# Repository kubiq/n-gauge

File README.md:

# N Gauge

A round AMOLED gauge that lives in the driver-side air vent of a **Hyundai
i30 N**, reading the car live over the OBD-II port: **oil temperature** - the
number the car's own dashboard hides behind a menu - plus coolant, boost, tyre
pressures, a g-meter, GPS speed and a lap timer. It logs every drive to an SD
card, uploads the logs home by itself as the car starts - over the phone's
hotspot and a WireGuard VPN - and a phone app pulls them off it and shows
each drive on a map.

Everything here was built for one car and is in daily use in it. It is a
hobby project, published in case the findings, the code or the approach help
someone with the same car or the same board.

*From the driver's seat, beside the car's own cluster; and switched off - the
3D-printed housing replaces the left air vent's surround.*

*The phone app: every drive, named after where it went and grouped by week,
with the gauge in the header - its last sync, like a watch in Garmin
Connect; a tap on it syncs, then the phone is back on the internet. A drive
on the map, coloured by speed, and its speed, boost, temperatures and
voltage over time. More in [mobile/](mobile).*

*The gauge's screens - oil and coolant, boost, the g-meter, tyres, GPS, and
the lap timer 1.8 s up on the best lap, the arc filling up to the line - then
the oil over its warning on the in-lap, a red rim over whichever screen is
up, and the N badge it wakes up with. Swiped through on the gauge; these are
from the [simulator](sim) on a made-up track session (`sim/screenshots.sh`).*

## What it does

- **Gauges:** oil and coolant (concentric arcs, with a cold-engine "not
  ready" state, and over-temperature warnings on every screen), boost, a
  g-meter, the four tyre pressures and temperatures, GPS speed and trip
  distance, a lap timer that finds the start/finish line by itself (tap START
  in the pit, then drive), with how far the line is and the live delta to the
  best lap.
- **Logging:** a CSV of every drive (2 Hz, decoded values - battery voltage,
  fuel rate, lambda, catalyst and fuel rail among them), a GPX track at
  25 Hz, a sleep log, and for each track session a Racelogic `.vbo` with
  every channel, which lap analysers open (HackTheTrack, Circuit Tools).
  Logs can be encrypted to a key only the phone holds, so a card taken out of
  the gauge gives nothing away. GPS points are kept only while the car talks
  or really moves, so a parked car's GPS drift is not a drive.
- **Upload home:** as the car starts - in the garage or setting off, where
  the GPS matters least - the gauge joins the phone's hotspot (a phone
  routine turns it on when it connects to the car's Bluetooth), opens a
  WireGuard tunnel into the home network and sends a small service on the
  home server ([server/](server)) whatever it lacks, resuming where the last
  upload stopped. The logs go as encrypted as they are on the card. Set up
  once in the app: the hotspot, the VPN (the gauge makes its own key; the app
  shows its public half for the router) and the server, with a time limit
  for how long the hotspot is the gauge's. Measured first, with a test build:
  transmitting costs ~6 dB of GNSS signal at any WiFi power, so it happens
  in the seconds an upload takes, not the whole drive. An optional status
  screen shows where it is - the hotspot, the VPN, the firmware download,
  the logs sent - and what came of the last one.
- **Waking up:** the N badge until the car answers, so the gauges never
  show a row of dashes; with a PC on USB, a status page for the desk.
- **Power:** deep sleep when the car goes quiet, ~11 mA parked (about 57
  days on the battery); wakes on CAN activity, the button, or the door
  opening (the IMU's wake-on-motion).
- **Firmware updates:** from the phone, the SD card or - by itself, after
  each upload of the logs, resuming a download that was cut off - the home
  server, signed (Ed25519) so it installs nothing else; on probation, rolled
  back if the new one fails.
- **Phone:** its own WiFi access point - with the upload set up, only once
  swiped to on the gauge, so the radio is free otherwise - with settings
  pages, OTA firmware
  updates with rollback, and an Android app ([mobile/](mobile)) that joins it
  from a QR code on the gauge, syncs the logs by itself and then lets go of
  the gauge's WiFi, so the phone is back on the internet. Each drive is
  named after where it started and ended (offline, from GeoNames - your own
  places like "Home" win), grouped by week, with its track on a map and its
  speed, boost, temperatures and voltage as charts. Delete a drive and it
  goes from the gauge too. A notification says when the gauge has a new
  drive (it puts a mark in its WiFi beacon), the synced drives can be saved
  to a folder by themselves, and the gauge's System card shows which part of
  it holds the internal RAM. English or Czech; dark themes or light.
- **Diagnostics:** a line per boot on the card (GPS rate, clock, CAN, RAM,
  why it last reset - and after a watchdog reset, which task it was), and
  the gauge's own WiFi repairs a join that got no address.

## Hardware

| Part | |
|---|---|
| Waveshare ESP32-S3-Touch-AMOLED-1.75 | 466×466 round AMOLED, touch, IMU, PMU, SD slot |
| SN65HVD230 | CAN transceiver, on OBD pins 6 and 14 |
| u-blox NEO-M9N | GNSS, 25 Hz |
| TPS5430 buck | 12 V → 5 V from OBD pin 16 |
| 3D-printed vent pod | replaces the left air vent; STLs in [mechanical/pod](mechanical/pod) |
| carrier PCB | KiCad, in [hardware/carrier](hardware/carrier) - replaces the breakout boards |

## Things worked out about the i30 N

Most of this took real drives and a lot of wrong turns; the reasoning, and
the wrong turns, are in [DECISIONS.md](DECISIONS.md).

- **Oil temperature is byte 34** of the Mode 22 reply to DID `0xE001` (engine
  ECU, `0x7E0`): `°C = raw × 0.7435 − 49.2`, matched against the dashboard up
  to 100 °C. Mode 01 PID `0x5C` is not supported. Byte 25 of the same reply
  *looks* like oil but is coolant-derived - and correlating bytes against the
  coolant curve picks it, which is how it was wrongly used for weeks.
- **Coolant as the dashboard shows it** is byte 25 of that reply, a few
  degrees below PID `0x05`.
- **Tyre pressures and temperatures** come from the TPMS module (`0x7A0`,
  DID `0xC00B`), not the ECU.
- **The OBD port is behind a gateway:** no broadcast traffic reaches it, only
  replies to requests - so brake, pedal and steering cannot be read passively
  there.
- **Gear** is derived from rpm ÷ speed; the measured ratios are in
  `config.h`.
- **Battery / charging voltage** is plain Mode 01 PID `0x42`: 14.4-15.0 V
  running, 9.9-10.6 V cranking, 12.1-12.7 V just after switching off. Then
  the ECU answers **0.00 V** for a few seconds before going quiet - drop
  it, it is not the battery.

## Repository

| Path | |
|---|---|
| [firmware/car_gauge_v1](firmware/car_gauge_v1) | the gauge firmware (Arduino, ESP32 core 3.x, LVGL 9) |
| [mobile](mobile) | the Android app (Expo / React Native) |
| [server](server) | the upload service the gauge sends its logs to (Python, Docker) |
| [sim](sim) | the gauge firmware on a PC: its screens in a window, fed a recorded drive |
| [tests](tests) | host tests of the firmware's pure logic |
| [hardware](hardware), [mechanical](mechanical) | carrier PCB, 3D-printed parts |
| [DECISIONS.md](DECISIONS.md) | why things are the way they are |
| [docs/flows.md](docs/flows.md) | how it decides, as diagrams: the logs' way, the upload, the WiFi, updates, screens, sleep |
| [PROTOTYPE_GUIDE.md](PROTOTYPE_GUIDE.md), [PRINTING_GUIDE.md](PRINTING_GUIDE.md) | wiring the prototype; printing the pod |

## Building

Firmware ([details](firmware/car_gauge_v1/README.md)):

```sh
./scripts/setup-libs.sh          # Arduino core, pinned libraries, lv_conf
./scripts/build.sh gauge flash   # compile and flash over USB
./scripts/test.sh                # host tests
./scripts/check.sh               # before a commit: tests, both firmware builds, the sim, the server
```

GitHub Actions ([.github/workflows/ci.yml](.github/workflows/ci.yml)) runs the
same checks but the simulator (it needs SDL2 from Ubuntu's mirrors, which
the runners could not reach for days), and the app's, on every push and pull
request. A version tag
(`git tag v2026.11.09 && git push --tags`) also makes a release: the firmware
as an update, and a full image for a first flash over USB. Releases carry the
public half of an update signing key if the repository variable `FW_SIGN_PUB`
holds one, and are signed if the secret `FW_SIGN_KEY` holds its private half
(64 hex digits) - the app then fetches the newest release by itself, checks
its signature against the gauge's key, and offers it in Gauge settings.

The upload server ([details](server/README.md)), on the home server:

```sh
cd server && echo "UPLOAD_TOKEN=$(openssl rand -hex 16)" > .env
docker compose up -d --build
```

With `FW_GITHUB_REPO=owner/name` in its `.env` it also passes that
repository's latest signed release on to the gauge, which then updates itself
([details](server/README.md#firmware-updates)). The signing key, once:

```sh
scripts/release-fw.py --init                 # then FW_SIGN_KEY and FW_SIGN_PUB on GitHub
```

The gauge on a PC ([details](sim/README.md)) - needs SDL2 and CMake:

```sh
sim/run.sh                       # the newest drive in data/, in a window
scripts/make_track_gpx.py        # a made-up track session to drive it with
sim/screenshots.sh               # these screenshots, into docs/gauge/
```

App ([details](mobile/README.md)):

```sh
cd mobile && ./scripts/build-apk.sh install   # release APK onto a phone over adb
```

## Caveats

- **Not affiliated with Hyundai.** "Hyundai", "i30 N" and the N badge used in
  the boot screen and the app icon are Hyundai's trademarks; they appear here
  only to say which car this is for.
- The gauge only **reads** - standard OBD and diagnostic requests, nothing
  that writes to the car. Still: it is your car, your OBD port and your
  responsibility, and a device on the dash must not distract from driving or
  sit in an airbag's path.
- Built and tested on one car, a European i30 N Fastback. Other model years
  or markets may answer differently.

## Licence

[MIT](LICENSE). Third-party assets keep their own licences - see
[firmware/assets/README.md](firmware/assets/README.md). The place names in
the app (`mobile/assets/places`) are from [GeoNames](https://www.geonames.org),
CC BY 4.0.

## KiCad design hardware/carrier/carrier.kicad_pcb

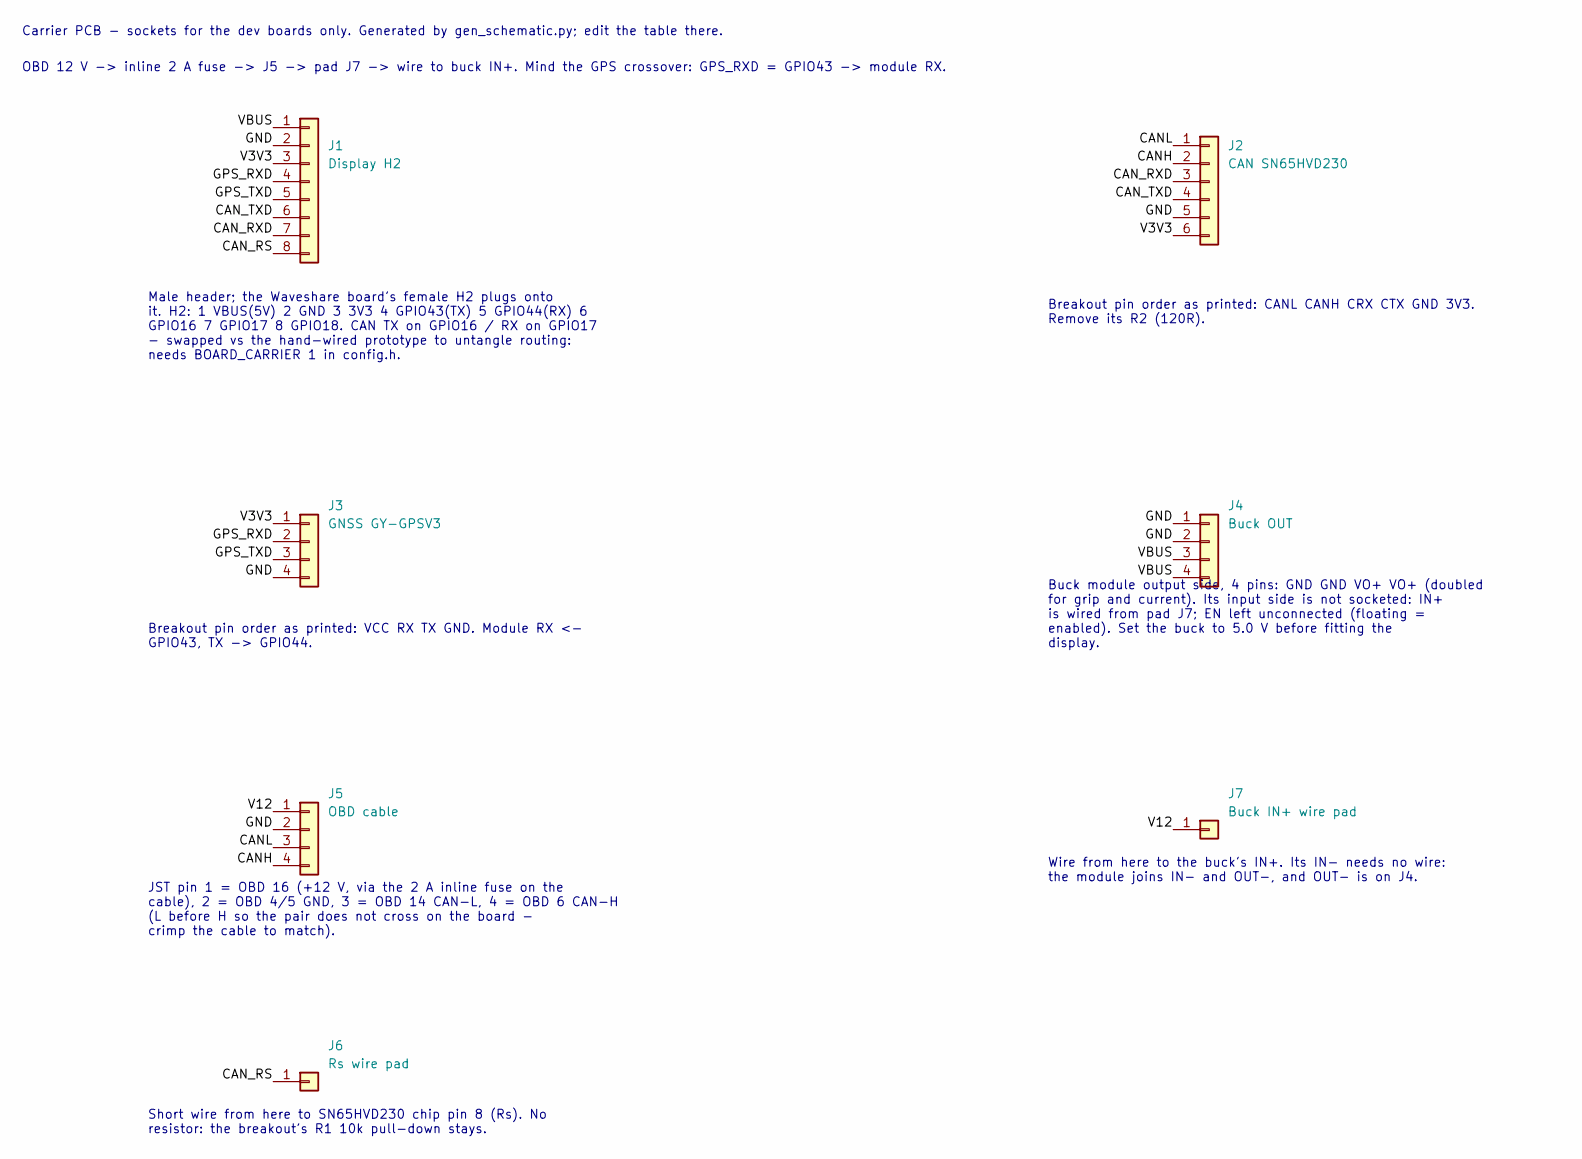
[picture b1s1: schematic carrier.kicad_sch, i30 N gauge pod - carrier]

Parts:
J1: Display H2; PinHeader_1x08_P2.54mm_Vertical
J2: CAN SN65HVD230; PinSocket_1x06_P2.54mm_Vertical
J3: GNSS GY-GPSV3; PinSocket_1x04_P2.54mm_Vertical
J4: Buck OUT; PinSocket_1x04_P2.54mm_Vertical
J5: OBD cable; JST_XH_B4B-XH-A_1x04_P2.50mm_Vertical
J6: Rs wire pad; TestPoint_THTPad_D2.0mm_Drill1.0mm
J7: Buck IN+ wire pad; TestPoint_THTPad_D2.0mm_Drill1.0mm

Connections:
CANH: J2.2, J5.4
CANL: J2.1, J5.3
CAN_RS: J1.8, J6.1
CAN_RXD: J1.7, J2.3
CAN_TXD: J1.6, J2.4
GND: J1.2, J2.5, J3.4, J4.1, J4.2, J5.2
GPS_RXD: J1.4, J3.2
GPS_TXD: J1.5, J3.3
V3V3: J1.3, J2.6, J3.1
V12: J5.1, J7.1
VBUS: J1.1, J4.3, J4.4

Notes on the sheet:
Male header; the Waveshare board's female H2 plugs onto it. H2: 1 VBUS(5V) 2 GND 3 3V3 4 GPIO43(TX) 5 GPIO44(RX) 6 GPIO16 7 GPIO17 8 GPIO18. CAN TX on GPIO16 / RX on GPIO17 - swapped vs the hand-wired prototype to untangle routing: needs BOARD_CARRIER 1 in config.h.
Breakout pin order as printed: CANL CANH CRX CTX GND 3V3. Remove its R2 (120R).
Breakout pin order as printed: VCC RX TX GND. Module RX <- GPIO43, TX -> GPIO44.
Buck module output side, 4 pins: GND GND VO+ VO+ (doubled for grip and current). Its input side is not socketed: IN+ is wired from pad J7; EN left unconnected (floating = enabled). Set the buck to 5.0 V before fitting the display.
JST pin 1 = OBD 16 (+12 V, via the 2 A inline fuse on the cable), 2 = OBD 4/5 GND, 3 = OBD 14 CAN-L, 4 = OBD 6 CAN-H (L before H so the pair does not cross on the board - crimp the cable to match).
Wire from here to the buck's IN+. Its IN- needs no wire: the module joins IN- and OUT-, and OUT- is on J4.
Short wire from here to SN65HVD230 chip pin 8 (Rs). No resistor: the breakout's R1 10k pull-down stays.
Carrier PCB - sockets for the dev boards only. Generated by gen_schematic.py; edit the table there.
OBD 12 V -> inline 2 A fuse -> J5 -> pad J7 -> wire to buck IN+. Mind the GPS crossover: GPS_RXD = GPIO43 -> module RX.

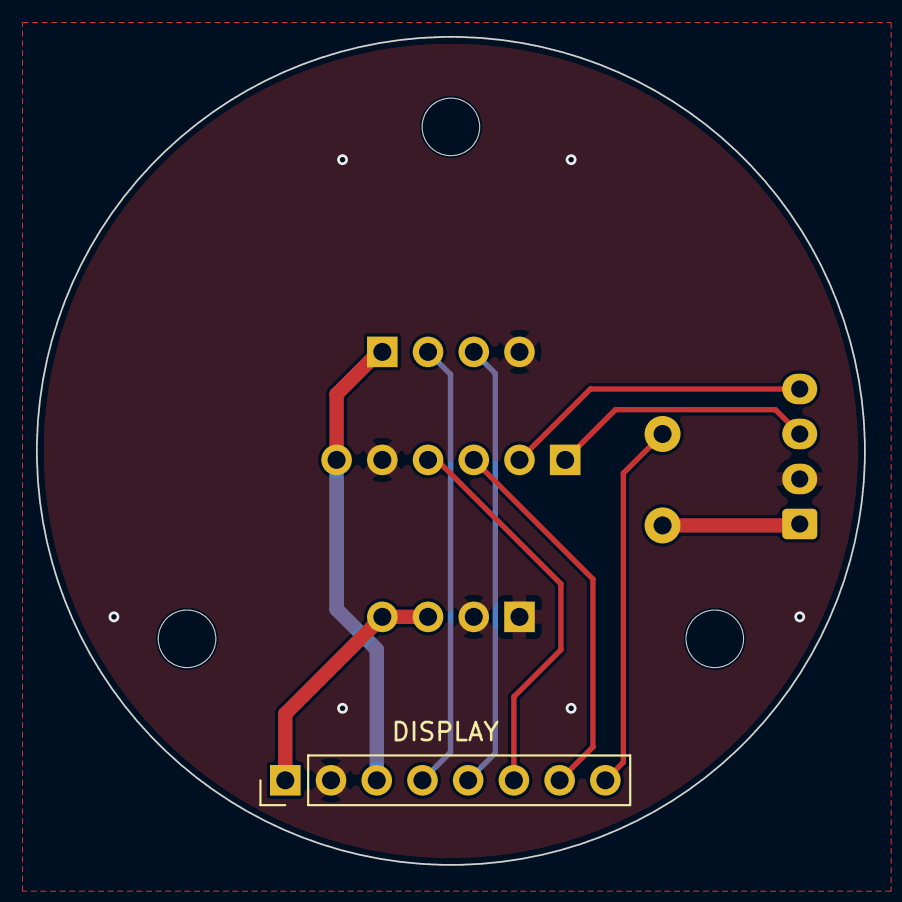
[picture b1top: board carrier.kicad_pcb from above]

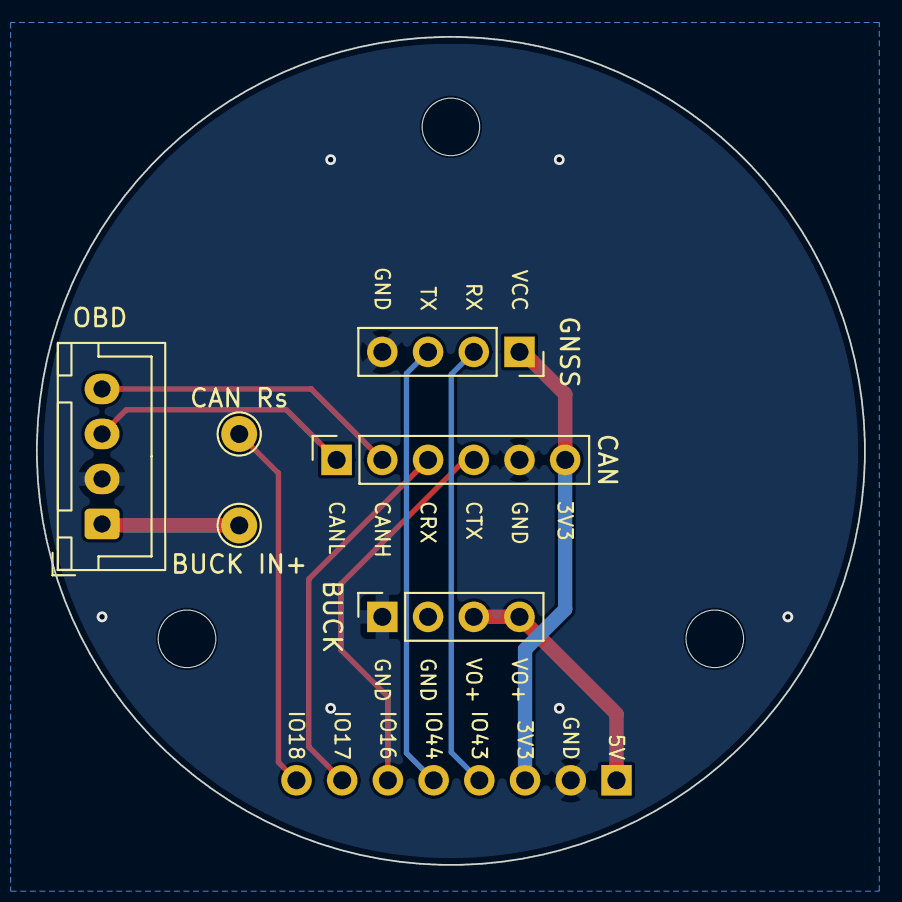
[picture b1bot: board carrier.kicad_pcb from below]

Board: 2 copper layers, 46.0 x 46.0 mm, 10 parts (6 on the bottom side), 11 nets.

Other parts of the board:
H1, H2, H3: M3 to pod; MountingHole_3.2mm_M3

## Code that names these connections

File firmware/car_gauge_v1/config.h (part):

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//   1 = the carrier PCB (hardware/carrier): TX GPIO16, RX GPIO17. Swapped
//       there so the pair runs straight to the transceiver socket instead of
//       crossing. Both 16 and 17 are RTC-capable, so either can be CAN_RX (the
//       ext1 wake source); CAN_RS stays on GPIO18 on both.
// The gauge has been on the carrier since 2026-10-18; 0 is for the prototype
// only. ⚠ The wrong one leaves CAN silent: TX and RX reversed.
#define BOARD_CARRIER      1
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// would sleep through the car starting. Confirm the part before trusting this.
//
// Wiring. The breakout does not bring Rs out to a header (only VCC/GND/RX/TX/
// CANH/CANL), so the wire goes onto IC pin 8 itself - a corner pin of the
// SOIC-8, the easiest on the package to tack onto - or onto the R1 pad that
// connects to it.
//
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// but it is out of spec - remove R2. It is a far more accessible part than
// pin 8.
#define CAN_RS_CONTROL     1
#define CAN_RS_GPIO        18     // freed by moving the GNSS UART to 43/44.
                                  // RTC-capable (0-21), and the pad hold in
                                  // obd_transceiver_standby() is measured to
                                  // survive deep sleep on it.
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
